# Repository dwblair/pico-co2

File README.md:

3xAA holder [keystone 2464 on digikey](https://www.digikey.com/en/products/detail/keystone-electronics/2464/303813?utm_adgroup=Battery%20Holders%2C%20Clips%2C%20Contacts&utm_source=google&utm_medium=cpc&utm_campaign=Shopping_Product_Battery%20Products&utm_term=&utm_content=Battery%20Holders%2C%20Clips%2C%20Contacts&gclid=Cj0KCQiA5NSdBhDfARIsALzs2EDxuh6IgCxwKD-gGiZrVjyGcqaCVPM8S2MJg16LCm9Hyk8qJxBTWYcaApDFEALw_wcB)

[keystone 2464 datasheet](https://www.keyelco.com/userAssets/file/M65p28.pdf)

3xAAA [keystone 2479](https://www.digikey.com/en/products/detail/keystone-electronics/2479/303824)

[AA and AAA Keystone battery holders datasheet](https://www.keyelco.com/userAssets/file/M65p28.pdf)

m2.5 wingnut [https://www.walmart.com/ip/M2-5-Stainless-Steel-Coarse-Female-Thread-Instal-Tool-Fastener-Wing-Nut-100pcs/139536392](https://www.walmart.com/ip/M2-5-Stainless-Steel-Coarse-Female-Thread-Instal-Tool-Fastener-Wing-Nut-100pcs/139536392)

m3 slotted thumb screw [https://www.digikey.com/en/products/detail/essentra-components/50M030050T005/11640409](https://www.digikey.com/en/products/detail/essentra-components/50M030050T005/11640409)

adalogger schematic [https://learn.adafruit.com/adafruit-adalogger-featherwing/downloads](https://learn.adafruit.com/adafruit-adalogger-featherwing/downloads)

PCF8523T RTC -- [https://www.digikey.com/en/products/detail/nxp-usa-inc/PCF8523T-1-118/2530422](https://www.digikey.com/en/products/detail/nxp-usa-inc/PCF8523T-1-118/2530422)

adafruit adalogger schematic [https://cdn-learn.adafruit.com/assets/assets/000/044/116/original/feather_schem.png?1500667618](https://cdn-learn.adafruit.com/assets/assets/000/044/116/original/feather_schem.png?1500667618)

32 khz crystal on digikey [https://www.digikey.com/en/products/detail/transko-electronics,-inc./CS31-32.768K-9-TR/13427726?utm_adgroup=Crystals&utm_source=google&utm_medium=cpc&utm_campaign=Shopping_DK%2BSupplier_Transko%20Electronics%20Inc&utm_term=&utm_content=Crystals&gclid=CjwKCAiA8OmdBhAgEiwAShr40zgUk4ZO5pCGyjE0bjxWT38Y2moxhUrvTism52RVnNrdhaW5F5u-MxoCXEMQAvD_BwE](https://www.digikey.com/en/products/detail/transko-electronics,-inc./CS31-32.768K-9-TR/13427726?utm_adgroup=Crystals&utm_source=google&utm_medium=cpc&utm_campaign=Shopping_DK%2BSupplier_Transko%20Electronics%20Inc&utm_term=&utm_content=Crystals&gclid=CjwKCAiA8OmdBhAgEiwAShr40zgUk4ZO5pCGyjE0bjxWT38Y2moxhUrvTism52RVnNrdhaW5F5u-MxoCXEMQAvD_BwE)

pcf8523T rtc [https://www.digikey.com/en/products/detail/nxp-usa-inc./PCF8523T%2F1,118/2530784?utm_adgroup=Integrated%20Circuits%20%28ICs%29&utm_source=google&utm_medium=cpc&utm_campaign=Shopping_Supplier_NXP%20USA%20Inc_0568_Co-op&utm_term=&utm_content=Integrated%20Circuits%20%28ICs%29&gclid=CjwKCAiA8OmdBhAgEiwAShr408KoTeQXFooxG_pMahZUPYFPXL6n5eyTnglh__SAioUxeqxWUZ0JkhoCWvAQAvD_BwE](https://www.digikey.com/en/products/detail/nxp-usa-inc./PCF8523T%2F1,118/2530784?utm_adgroup=Integrated%20Circuits%20%28ICs%29&utm_source=google&utm_medium=cpc&utm_campaign=Shopping_Supplier_NXP%20USA%20Inc_0568_Co-op&utm_term=&utm_content=Integrated%20Circuits%20%28ICs%29&gclid=CjwKCAiA8OmdBhAgEiwAShr408KoTeQXFooxG_pMahZUPYFPXL6n5eyTnglh__SAioUxeqxWUZ0JkhoCWvAQAvD_BwE)

crystal -- abracon abs25 -- [https://www.digikey.com/en/products/detail/abracon-llc/ABS25-32-768KHZ-T/675361](https://www.digikey.com/en/products/detail/abracon-llc/ABS25-32-768KHZ-T/675361)

keystone 1056 battery holder for cr1220 [https://www.digikey.com/en/products/detail/keystone-electronics/1056/2020198?utm_adgroup=Battery%20Holders%2C%20Clips%2C%20Contacts&utm_source=google&utm_medium=cpc&utm_campaign=Shopping_Product_Battery%20Products&utm_term=&utm_content=Battery%20Holders%2C%20Clips%2C%20Contacts&gclid=CjwKCAiAk--dBhABEiwAchIwkUNj9rHFoMsa1-F4Yangn19e-GtB8Dxxvhv1THlc-r7Txwer6lv5VhoCUtkQAvD_BwE](https://www.digikey.com/en/products/detail/keystone-electronics/1056/2020198?utm_adgroup=Battery%20Holders%2C%20Clips%2C%20Contacts&utm_source=google&utm_medium=cpc&utm_campaign=Shopping_Product_Battery%20Products&utm_term=&utm_content=Battery%20Holders%2C%20Clips%2C%20Contacts&gclid=CjwKCAiAk--dBhABEiwAchIwkUNj9rHFoMsa1-F4Yangn19e-GtB8Dxxvhv1THlc-r7Txwer6lv5VhoCUtkQAvD_BwE)

keystone 1056 datasheet [https://www.keyelco.com/userAssets/file/M65p2.pdf](https://www.keyelco.com/userAssets/file/M65p2.pdf)

feather m0 lora schematic [https://cdn-learn.adafruit.com/assets/assets/000/032/914/original/feather_schem.png?1465421956](https://cdn-learn.adafruit.com/assets/assets/000/032/914/original/feather_schem.png?1465421956)

mcp73831 batt charger [https://www.digikey.com/en/products/detail/microchip-technology/MCP73831T-4ADI%2FOT/9642871?utm_adgroup=Integrated%20Circuits&utm_source=google&utm_medium=cpc&utm_campaign=Shopping_Supplier_Microchip_0150_Co-op&utm_term=&utm_content=Integrated%20Circuits&gclid=CjwKCAiAk--dBhABEiwAchIwkf7PnDEnhvXVZeDLD8DRrhM5UvXJwGeDoK-BSZtsmEc21kOQQNOWFRoC6VEQAvD_BwE](https://www.digikey.com/en/products/detail/microchip-technology/MCP73831T-4ADI%2FOT/9642871?utm_adgroup=Integrated%20Circuits&utm_source=google&utm_medium=cpc&utm_campaign=Shopping_Supplier_Microchip_0150_Co-op&utm_term=&utm_content=Integrated%20Circuits&gclid=CjwKCAiAk--dBhABEiwAchIwkf7PnDEnhvXVZeDLD8DRrhM5UvXJwGeDoK-BSZtsmEc21kOQQNOWFRoC6VEQAvD_BwE)

mbr120 diodes [https://www.digikey.com/en/products/detail/onsemi/MBR120LSFT3G/1477155](https://www.digikey.com/en/products/detail/onsemi/MBR120LSFT3G/1477155)

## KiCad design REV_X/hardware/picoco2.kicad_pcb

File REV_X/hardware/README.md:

3xAA holder [keystone 2464 on digikey](https://www.digikey.com/en/products/detail/keystone-electronics/2464/303813?utm_adgroup=Battery%20Holders%2C%20Clips%2C%20Contacts&utm_source=google&utm_medium=cpc&utm_campaign=Shopping_Product_Battery%20Products&utm_term=&utm_content=Battery%20Holders%2C%20Clips%2C%20Contacts&gclid=Cj0KCQiA5NSdBhDfARIsALzs2EDxuh6IgCxwKD-gGiZrVjyGcqaCVPM8S2MJg16LCm9Hyk8qJxBTWYcaApDFEALw_wcB)

[keystone 2464 datasheet](https://www.keyelco.com/userAssets/file/M65p28.pdf)

3xAAA [keystone 2479](https://www.digikey.com/en/products/detail/keystone-electronics/2479/303824)

[AA and AAA Keystone battery holders datasheet](https://www.keyelco.com/userAssets/file/M65p28.pdf)

m2.5 wingnut [https://www.walmart.com/ip/M2-5-Stainless-Steel-Coarse-Female-Thread-Instal-Tool-Fastener-Wing-Nut-100pcs/139536392](https://www.walmart.com/ip/M2-5-Stainless-Steel-Coarse-Female-Thread-Instal-Tool-Fastener-Wing-Nut-100pcs/139536392)

m3 slotted thumb screw [https://www.digikey.com/en/products/detail/essentra-components/50M030050T005/11640409](https://www.digikey.com/en/products/detail/essentra-components/50M030050T005/11640409)

adalogger schematic [https://learn.adafruit.com/adafruit-adalogger-featherwing/downloads](https://learn.adafruit.com/adafruit-adalogger-featherwing/downloads)

PCF8523T RTC -- [https://www.digikey.com/en/products/detail/nxp-usa-inc/PCF8523T-1-118/2530422](https://www.digikey.com/en/products/detail/nxp-usa-inc/PCF8523T-1-118/2530422)

adafruit adalogger schematic [https://cdn-learn.adafruit.com/assets/assets/000/044/116/original/feather_schem.png?1500667618](https://cdn-learn.adafruit.com/assets/assets/000/044/116/original/feather_schem.png?1500667618)

32 khz crystal on digikey [https://www.digikey.com/en/products/detail/transko-electronics,-inc./CS31-32.768K-9-TR/13427726?utm_adgroup=Crystals&utm_source=google&utm_medium=cpc&utm_campaign=Shopping_DK%2BSupplier_Transko%20Electronics%20Inc&utm_term=&utm_content=Crystals&gclid=CjwKCAiA8OmdBhAgEiwAShr40zgUk4ZO5pCGyjE0bjxWT38Y2moxhUrvTism52RVnNrdhaW5F5u-MxoCXEMQAvD_BwE](https://www.digikey.com/en/products/detail/transko-electronics,-inc./CS31-32.768K-9-TR/13427726?utm_adgroup=Crystals&utm_source=google&utm_medium=cpc&utm_campaign=Shopping_DK%2BSupplier_Transko%20Electronics%20Inc&utm_term=&utm_content=Crystals&gclid=CjwKCAiA8OmdBhAgEiwAShr40zgUk4ZO5pCGyjE0bjxWT38Y2moxhUrvTism52RVnNrdhaW5F5u-MxoCXEMQAvD_BwE)

pcf8523T rtc [https://www.digikey.com/en/products/detail/nxp-usa-inc./PCF8523T%2F1,118/2530784?utm_adgroup=Integrated%20Circuits%20%28ICs%29&utm_source=google&utm_medium=cpc&utm_campaign=Shopping_Supplier_NXP%20USA%20Inc_0568_Co-op&utm_term=&utm_content=Integrated%20Circuits%20%28ICs%29&gclid=CjwKCAiA8OmdBhAgEiwAShr408KoTeQXFooxG_pMahZUPYFPXL6n5eyTnglh__SAioUxeqxWUZ0JkhoCWvAQAvD_BwE](https://www.digikey.com/en/products/detail/nxp-usa-inc./PCF8523T%2F1,118/2530784?utm_adgroup=Integrated%20Circuits%20%28ICs%29&utm_source=google&utm_medium=cpc&utm_campaign=Shopping_Supplier_NXP%20USA%20Inc_0568_Co-op&utm_term=&utm_content=Integrated%20Circuits%20%28ICs%29&gclid=CjwKCAiA8OmdBhAgEiwAShr408KoTeQXFooxG_pMahZUPYFPXL6n5eyTnglh__SAioUxeqxWUZ0JkhoCWvAQAvD_BwE)

crystal -- abracon abs25 -- [https://www.digikey.com/en/products/detail/abracon-llc/ABS25-32-768KHZ-T/675361](https://www.digikey.com/en/products/detail/abracon-llc/ABS25-32-768KHZ-T/675361)

keystone 1056 battery holder for cr1220 [https://www.digikey.com/en/products/detail/keystone-electronics/1056/2020198?utm_adgroup=Battery%20Holders%2C%20Clips%2C%20Contacts&utm_source=google&utm_medium=cpc&utm_campaign=Shopping_Product_Battery%20Products&utm_term=&utm_content=Battery%20Holders%2C%20Clips%2C%20Contacts&gclid=CjwKCAiAk--dBhABEiwAchIwkUNj9rHFoMsa1-F4Yangn19e-GtB8Dxxvhv1THlc-r7Txwer6lv5VhoCUtkQAvD_BwE](https://www.digikey.com/en/products/detail/keystone-electronics/1056/2020198?utm_adgroup=Battery%20Holders%2C%20Clips%2C%20Contacts&utm_source=google&utm_medium=cpc&utm_campaign=Shopping_Product_Battery%20Products&utm_term=&utm_content=Battery%20Holders%2C%20Clips%2C%20Contacts&gclid=CjwKCAiAk--dBhABEiwAchIwkUNj9rHFoMsa1-F4Yangn19e-GtB8Dxxvhv1THlc-r7Txwer6lv5VhoCUtkQAvD_BwE)

keystone 1056 datasheet [https://www.keyelco.com/userAssets/file/M65p2.pdf](https://www.keyelco.com/userAssets/file/M65p2.pdf)

feather m0 lora schematic [https://cdn-learn.adafruit.com/assets/assets/000/032/914/original/feather_schem.png?1465421956](https://cdn-learn.adafruit.com/assets/assets/000/032/914/original/feather_schem.png?1465421956)

mcp73831 batt charger [https://www.digikey.com/en/products/detail/microchip-technology/MCP73831T-4ADI%2FOT/9642871?utm_adgroup=Integrated%20Circuits&utm_source=google&utm_medium=cpc&utm_campaign=Shopping_Supplier_Microchip_0150_Co-op&utm_term=&utm_content=Integrated%20Circuits&gclid=CjwKCAiAk--dBhABEiwAchIwkf7PnDEnhvXVZeDLD8DRrhM5UvXJwGeDoK-BSZtsmEc21kOQQNOWFRoC6VEQAvD_BwE](https://www.digikey.com/en/products/detail/microchip-technology/MCP73831T-4ADI%2FOT/9642871?utm_adgroup=Integrated%20Circuits&utm_source=google&utm_medium=cpc&utm_campaign=Shopping_Supplier_Microchip_0150_Co-op&utm_term=&utm_content=Integrated%20Circuits&gclid=CjwKCAiAk--dBhABEiwAchIwkf7PnDEnhvXVZeDLD8DRrhM5UvXJwGeDoK-BSZtsmEc21kOQQNOWFRoC6VEQAvD_BwE)

mbr120 diodes [https://www.digikey.com/en/products/detail/onsemi/MBR120LSFT3G/1477155](https://www.digikey.com/en/products/detail/onsemi/MBR120LSFT3G/1477155)

digikey version of ssd1306 display: [https://www.digikey.com/en/products/detail/universal-solder-electronics-ltd/OLED%2520128X64%25201.3%2522%2520I2C/16822118?utm_adgroup=Display%20Modules%20-%20LCD%2C%20OLED%20Character%20and%20Numeric&utm_source=google&utm_medium=cpc&utm_campaign=Shopping_Product_Optoelectronics&utm_term=&utm_content=Display%20Modules%20-%20LCD%2C%20OLED%20Character%20and%20Numeric&gclid=Cj0KCQiAq5meBhCyARIsAJrtdr6MQLcgHrdY2lsyDV9M3TC22ROxltBemC9oLMb8EUAJi6iq65Skr48aAoGtEALw_wcB](https://www.digikey.com/en/products/detail/universal-solder-electronics-ltd/OLED%2520128X64%25201.3%2522%2520I2C/16822118?utm_adgroup=Display%20Modules%20-%20LCD%2C%20OLED%20Character%20and%20Numeric&utm_source=google&utm_medium=cpc&utm_campaign=Shopping_Product_Optoelectronics&utm_term=&utm_content=Display%20Modules%20-%20LCD%2C%20OLED%20Character%20and%20Numeric&gclid=Cj0KCQiAq5meBhCyARIsAJrtdr6MQLcgHrdY2lsyDV9M3TC22ROxltBemC9oLMb8EUAJi6iq65Skr48aAoGtEALw_wcB)

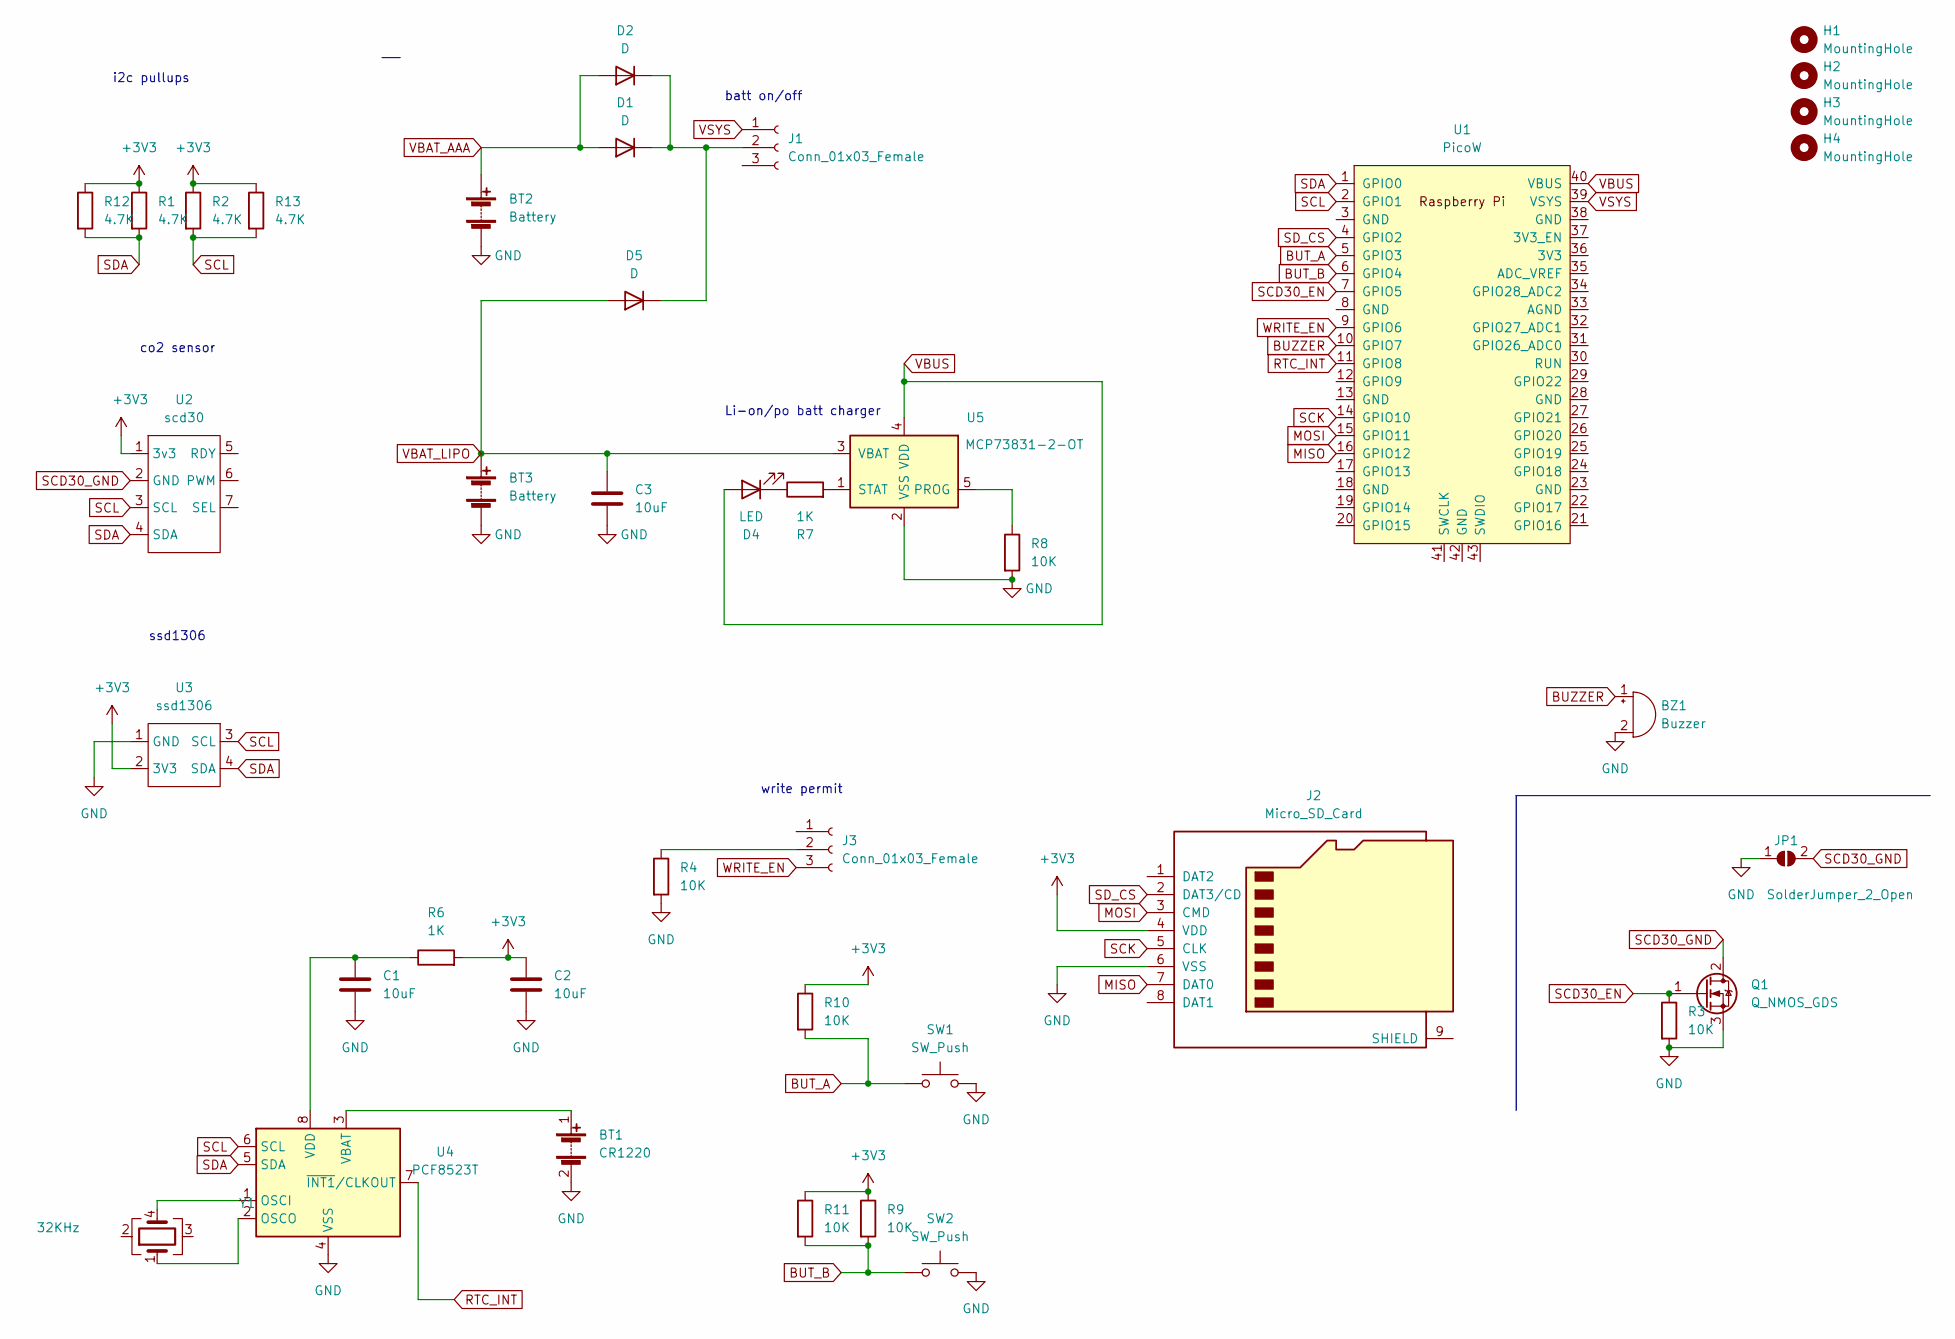
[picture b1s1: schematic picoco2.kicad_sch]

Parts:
BT1: CR1220; CR1220-2
BT2: Battery; BatteryHolder_Keystone_2468_2xAAA
BT3: Battery; JST_PH_S2B-PH-SM4-TB_1x02-1MP_P2.00mm_Horizontal
BZ1: Buzzer; MagneticBuzzer_Kobitone_254-EMB84Q-RO
C1, C2, C3: 10uF; C_0603_1608Metric_Pad1.08x0.95mm_HandSolder
D1, D5: D; D_SOD-123F
D2: D; D_5W_P10.16mm_Horizontal
D4: LED; LED_0603_1608Metric_Pad1.05x0.95mm_HandSolder
H1, H2, H3, H4: MountingHole; MountingHole_3.2mm_M3
J1, J3: Conn_01x03_Female; PinSocket_1x03_P2.54mm_Vertical
J2: Micro_SD_Card; DM3D-SF_outline
JP1: SolderJumper_2_Open; SolderJumper-2_P1.3mm_Open_Pad1.0x1.5mm
Q1: Q_NMOS_GDS; SOT-23
R1, R2: 4.7K; R_0603_1608Metric_Pad0.98x0.95mm_HandSolder
R3, R4, R8, R9: 10K; R_0603_1608Metric_Pad0.98x0.95mm_HandSolder
R6, R7: 1K; R_0603_1608Metric_Pad0.98x0.95mm_HandSolder
R10, R11: 10K; R_Axial_DIN0204_L3.6mm_D1.6mm_P7.62mm_Horizontal
R12, R13: 4.7K; R_Axial_DIN0204_L3.6mm_D1.6mm_P7.62mm_Horizontal
SW1, SW2: SW_Push; SW_Tactile_SPST_Angled_PTS645Vx31-2LFS
U1: PicoW; RPi_PicoW_SMD
U2: scd30; scd30_a
U3: ssd1306; ssd1306_a
U4: PCF8523T; SOIC-8_3.9x4.9mm_P1.27mm
U5: MCP73831-2-OT; SOT-23-5
Y1: 32KHz; Crystal_SMD_Abracon_ABS25-4Pin_8.0x3.8mm

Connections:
+3V3: C2.1, J2.4 (VDD), R1.1, R2.1, R6.2, R9.1, R10.1, R11.1, R12.1, R13.1, U2.1 (3v3), U3.2 (3V3)
BUT_A: R10.2, SW1.1, U1.5 (GPIO3)
BUT_B: R9.2, R11.2, SW2.1, U1.6 (GPIO4)
BUZZER: BZ1.1 (-), U1.10 (GPIO7)
GND: BT1.2 (-), BT2.2 (-), BT3.2 (-), BZ1.2 (+), C1.2, C2.2, C3.2, J2.6 (VSS), JP1.1 (A), Q1.3 (S), R3.2, R4.2, R8.2, SW1.2, SW2.2, U3.1 (GND), U4.4 (VSS), U5.2 (VSS)
MISO: J2.7 (DAT0), U1.16 (GPIO12)
MOSI: J2.3 (CMD), U1.15 (GPIO11)
unnamed: BT1.1 (+), U4.3 (VBAT)
unnamed: C1.1, R6.1, U4.8 (VDD)
unnamed: D1.1 (K), D2.1 (K), D5.1 (K), J1.2
unnamed: D4.1 (K), R7.1
unnamed: J3.2, R4.1
unnamed: R7.2, U5.1 (STAT)
unnamed: R8.1, U5.5 (PROG)
unnamed: U4.1 (OSCI), Y1.4
unnamed: U4.2 (OSCO), Y1.1
RTC_INT: U1.11 (GPIO8), U4.7 (~INT1/CLKOUT)
SCD30_EN: Q1.1 (G), R3.1, U1.7 (GPIO5)
SCD30_GND: JP1.2 (B), Q1.2 (D), U2.2 (GND)
SCK: J2.5 (CLK), U1.14 (GPIO10)
SCL: R2.2, R13.2, U1.2 (GPIO1), U2.3 (SCL), U3.3 (SCL), U4.6 (SCL)
SDA: R1.2, R12.2, U1.1 (GPIO0), U2.4 (SDA), U3.4 (SDA), U4.5 (SDA)
SD_CS: J2.2 (DAT3/CD), U1.4 (GPIO2)
VBAT_AAA: BT2.1 (+), D1.2 (A), D2.2 (A)
VBAT_LIPO: BT3.1 (+), C3.1, D5.2 (A), U5.3 (VBAT)
VBUS: D4.2 (A), U1.40 (VBUS), U5.4 (VDD)
VSYS: J1.1, U1.39 (VSYS)
WRITE_EN: J3.3, U1.9 (GPIO6)

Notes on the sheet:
i2c pullups
write permit
batt on/off
Li-on/po batt charger
co2 sensor
ssd1306

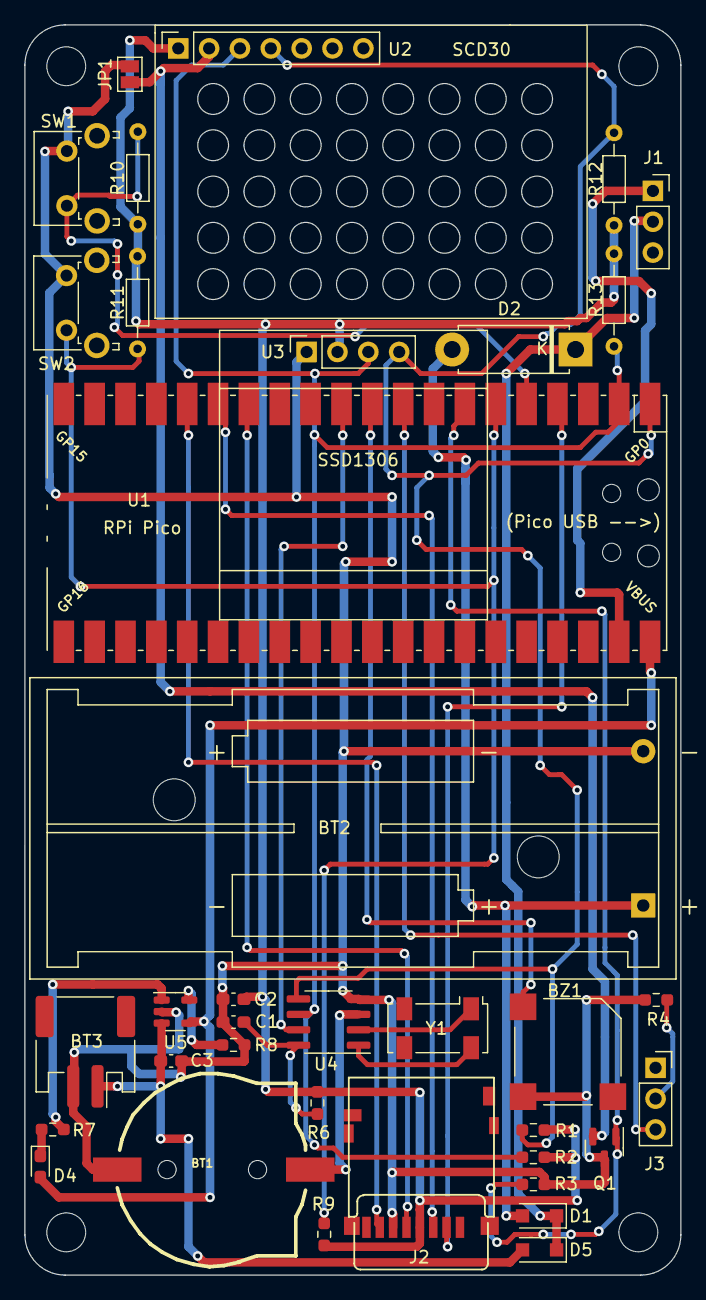
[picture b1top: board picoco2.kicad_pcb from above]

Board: 2 copper layers, 54.0 x 102.9 mm, 40 parts (0 on the bottom side), 28 nets.

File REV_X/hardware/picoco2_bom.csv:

"Id";"Designator";"Package";"Quantity";"Designation";"Supplier and ref";
1;"J2";"DM3D-SF_outline";1;"Micro_SD_Card";;;
2;"U4";"SOIC-8_3.9x4.9mm_P1.27mm";1;"PCF8523T";;;
3;"C2,C1,C3";"C_0603_1608Metric_Pad1.08x0.95mm_HandSolder";3;"10uF";;;
4;"R13,R12";"R_Axial_DIN0204_L3.6mm_D1.6mm_P7.62mm_Horizontal";2;"4.7K";;;
5;"J3,J1";"PinSocket_1x03_P2.54mm_Vertical";2;"Conn_01x03_Female";;;
6;"H3,H1,H2,H4";"MountingHole_3.2mm_M3";4;"MountingHole";;;
7;"BT2";"BatteryHolder_Keystone_2468_2xAAA";1;"Battery";;;
8;"SW2,SW1";"SW_Tactile_SPST_Angled_PTS645Vx31-2LFS";2;"SW_Push";;;
9;"R3,R8,R9";"R_0603_1608Metric_Pad0.98x0.95mm_HandSolder";3;"10K";;;
10;"U3";"ssd1306_a";1;"ssd1306";;;
11;"R11,R10";"R_Axial_DIN0204_L3.6mm_D1.6mm_P7.62mm_Horizontal";2;"10K";;;
12;"Q1";"SOT-23";1;"Q_NMOS_GDS";;;
13;"R6,R7";"R_0603_1608Metric_Pad0.98x0.95mm_HandSolder";2;"1K";;;
14;"U5";"SOT-23-5";1;"MCP73831-2-OT";;;
15;"D1,D5";"D_SOD-123F";2;"D";;;
16;"BT3";"JST_PH_S2B-PH-SM4-TB_1x02-1MP_P2.00mm_Horizontal";1;"Battery";;;
17;"BT1";"CR1220-2";1;"CR1220";;;
18;"U1";"RPi_PicoW_SMD";1;"PicoW";;;
19;"R4";"R_0603_1608Metric_Pad0.98x0.95mm_HandSolder";1;"R";;;
20;"R1,R2";"R_0603_1608Metric_Pad0.98x0.95mm_HandSolder";2;"4.7K";;;
21;"JP1";"SolderJumper-2_P1.3mm_Open_Pad1.0x1.5mm";1;"SolderJumper_2_Open";;;
22;"D4";"LED_0603_1608Metric_Pad1.05x0.95mm_HandSolder";1;"LED";;;
23;"BZ1";"MagneticBuzzer_Kobitone_254-EMB84Q-RO";1;"Buzzer";;;
24;"Y1";"Crystal_SMD_Abracon_ABS25-4Pin_8.0x3.8mm";1;"32KHz";;;
25;"U2";"scd30_a";1;"scd30";;;
26;"D2";"D_5W_P10.16mm_Horizontal";1;"D";;;

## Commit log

2023-01-11 basic layout done
2023-01-11 rounded edges
2023-01-12 added i2c resistors
2023-01-15 finished positioning of holes and parts
2023-01-15 routed power lines
2023-01-16 finally finished routing power
2023-01-16 full routing
2023-01-16 full routing 2
2023-01-16 fully routed
2023-01-20 fully routed, revised ssd1306 display module
2023-01-20 added label for ssd1306
2023-01-20 avoided copper keepouts
2023-01-20 recentered the display
2023-01-20 cover, revised base, back
2023-01-20 minor cosmetics
2023-02-11 updated values on components
